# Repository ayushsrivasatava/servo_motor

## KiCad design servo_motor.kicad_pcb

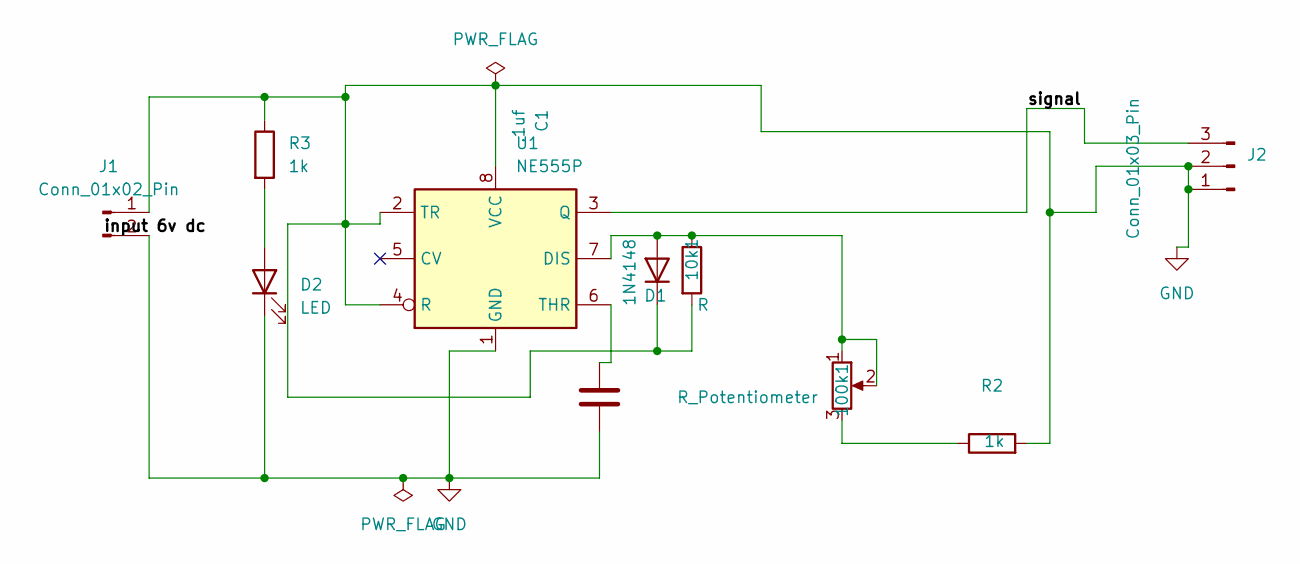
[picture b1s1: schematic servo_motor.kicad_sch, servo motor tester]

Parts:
10k1: R; R_Axial_DIN0204_L3.6mm_D1.6mm_P5.08mm_Horizontal
100k1: R_Potentiometer; Potentiometer_Vishay_148-149_Single_Horizontal
C1: .1uf; C_Disc_D3.4mm_W2.1mm_P2.50mm
D1: 1N4148; D_DO-35_SOD27_P7.62mm_Horizontal
D2: LED; LED_D1.8mm_W1.8mm_H2.4mm_Horizontal_O3.81mm_Z4.9mm
J1: Conn_01x02_Pin; PinHeader_1x02_P2.54mm_Horizontal
J2: Conn_01x03_Pin; PinHeader_1x03_P2.54mm_Horizontal
R2: 1k; R_Axial_DIN0207_L6.3mm_D2.5mm_P5.08mm_Vertical
R3: 1k; R_Axial_DIN0207_L6.3mm_D2.5mm_P7.62mm_Horizontal
U1: NE555P; DIP-8_W7.62mm

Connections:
/signal: J2.3, U1.3 (Q)
GND: 10k1.2, C1.2, D1.1 (K), D2.1 (K), J1.1, J1.2, J2.1, J2.2, R2.2, R3.1, U1.1 (GND), U1.2 (TR), U1.4 (R), U1.8 (VCC)
unnamed: 100k1.3, R2.1
unnamed: 10k1.1, 100k1.1, 100k1.2, D1.2 (A), U1.7 (DIS)
unnamed: D2.2 (A), R3.2
unnamed: C1.1, U1.6 (THR)

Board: 2 copper layers, 10 parts (0 on the bottom side), 6 nets, no tracks yet.

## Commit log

2025-07-01 add servo motor control code
